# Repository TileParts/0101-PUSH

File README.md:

0101-PUSH
==========

一个简易的 8.5mm 开关，附带 LED 指示灯。

## 特性

1. 预留了上拉/下拉、高电平有效/低电平有效的配置电阻
2. 预留消抖电容
3. 附带 LED 指示灯

## 协议

[CERN-OHL-P-2.0](LICENSE)

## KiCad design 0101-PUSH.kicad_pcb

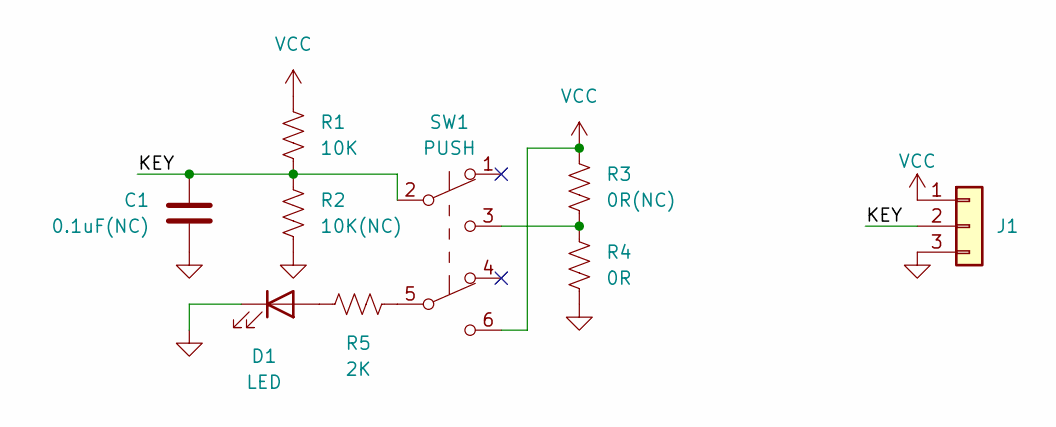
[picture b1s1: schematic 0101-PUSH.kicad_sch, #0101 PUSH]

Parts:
C1: 0.1uF(NC); C_0402_1005Metric
D1: LED; LED_0603_1608Metric; PartNumber C72041
J1: Conn_01x03; PinHeader_1x03_P2.54mm_Vertical
R1: 10K; R_0603_1608Metric; PartNumber C25804
R2: 10K(NC); R_0603_1608Metric
R3: 0R(NC); R_0603_1608Metric
R4: 0R; R_0603_1608Metric; PartNumber C21189
R5: 2K; R_0402_1005Metric; PartNumber C4109
SW1: PUSH; SW_Push_DPDT_8.5x8.5mm; PartNumber C194405

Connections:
/KEY: C1.1, J1.2, R1.2, R2.1, SW1.2 (B)
GND: C1.2, D1.1 (K), J1.3, R2.2, R4.2
unnamed: D1.2 (A), R5.1
unnamed: R3.2, R4.1, SW1.3 (C)
unnamed: R5.2, SW1.5 (B)
VCC: J1.1, R1.1, R3.1, SW1.6 (C)

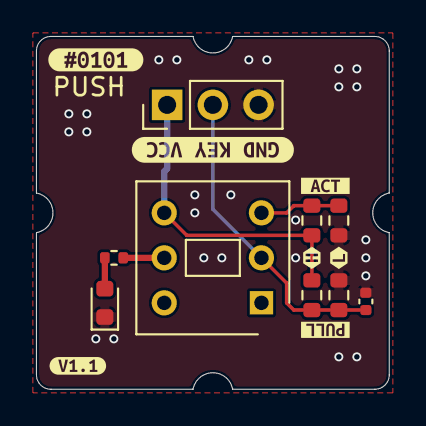
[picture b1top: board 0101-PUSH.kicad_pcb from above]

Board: 2 copper layers, 19.6 x 19.6 mm, 16 parts (0 on the bottom side), 6 nets.

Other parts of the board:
kibuzzard-631DDDB8: G***; kibuzzard-631DDDB8
kibuzzard-632ECE43: G***; kibuzzard-632ECE43
kibuzzard-6324301C: G***; kibuzzard-6324301C
kibuzzard-63243463: G***; kibuzzard-63243463
kibuzzard-63243468: G***; kibuzzard-63243468
kibuzzard-63243772: G***; kibuzzard-63243772
kibuzzard-63243779: G***; kibuzzard-63243779

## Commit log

2022-09-11 Init repository
2022-09-11 Add #0101 PUSH
2022-09-11 Migrate to KiCad 6
2022-09-11 Finish
2022-09-11 Use kibuzzard silk
2022-09-12 Update PCB settings
2022-09-12 Update pull-up/down resistors
2022-09-12 Add README
2022-09-12 Output gerber V1.0
2022-09-24 Rework with new design
2022-09-24 Output MF docs V1.1
